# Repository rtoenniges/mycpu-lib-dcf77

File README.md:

# MyCPU_LIB_DCF77
A library written in assembler for the [MyCPU](http://www.mycpu.eu/) from Dennis Kuschel to decode the DCF77-Signal provided by an edge detection circuit.

Works also with the SCC-Rack Extension [MyCPU_PRO_SCC](https://github.com/rtoenniges/mycpu-project-slaveclock/tree/master).

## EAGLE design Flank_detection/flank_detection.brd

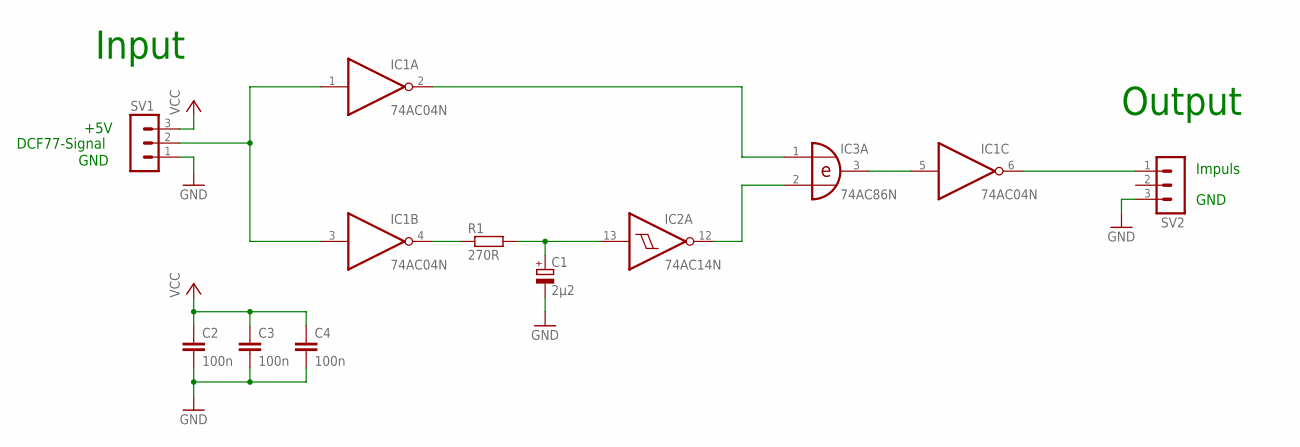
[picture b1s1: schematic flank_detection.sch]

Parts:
C1: 2µ2; E2,5-6E
C2, C3, C4: 100n; C050-024X044
IC1: 74AC04N; DIL14
IC2: 74AC14N; DIL14
IC3: 74AC86N; DIL14
R1: 270R; 0204/5
SV1, SV2: MA03-1

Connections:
GND: C1.-, C2.2, C3.2, C4.2, IC1.7 (GND), IC2.7 (GND), IC3.7 (GND), SV1.1, SV2.3
unnamed: IC1.1 (I), IC1.3 (I), SV1.2
unnamed: IC1.4 (O), R1.1
unnamed: C1.+, IC2.13 (I), R1.2
unnamed: IC1.2 (O), IC3.1 (I0)
unnamed: IC2.12 (O), IC3.2 (I1)
unnamed: IC1.5 (I), IC3.3 (O)
unnamed: IC1.6 (O), SV2.1
VCC: C2.1, C3.1, C4.1, IC1.14 (VCC), IC2.14 (VCC), IC3.14 (VCC), SV1.3

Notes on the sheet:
Input
Output
+5V
DCF77-Signal
GND
Impuls

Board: 2 copper layers, 10 parts (0 on the bottom side), 9 nets, no tracks yet.

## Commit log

2016-03-18 Added files via upload
2016-03-18 Rename sl60dcf77.asm to asm/sl60dcf77.asm
2016-03-18 Translate the comments
    Translate comments from german to english
2016-03-18 Translate comments
    Translated comments from german to english
2016-03-28 Additional comments
2016-03-28 Changed comment
2016-03-29 Listfile update
2016-03-29 Revert "Listfile update"
    This reverts commit 2b88d5d4967de4d4c234f793891d0606d7fe10c6.
2016-03-29 New feature to display synced status
    Synced status can now be displayed on the Multi-I/O-LEDs (default
    enabled).
    See "#DEFINE SYNC_DISP" line in programm
2016-03-29 Listfile updated
2016-03-31 Update and debug
    Little bit code optimizing and fixed a bug in partity checking
2016-03-31 Update and fixes
    Little bit code optimizing and fixed a bug in partity checking
2016-04-14 Move program to seperate memory page
    To save "program ram" program moved into "paged data ram"
2016-10-13 Updatet sync display and fixed error on lib calls
2017-02-20 Optimization and bug fixing
    Many many code optimizations (Memory and speed).
    Bug fixes (Mainly one big bug that couses the library to work only every
    second year)
2017-02-24 Bug fixes
2017-03-20 Added licence
2017-03-21 Edited board
2017-05-03 Add scc board
    Added #define for the scc-rack-extension
    Default is commented out
2017-05-09 Bug fix in SYNC_DISP
2017-05-10 Fixed bug in sync display
2017-05-11 Little optimizing
    In case of de synchronization more code will be skipped
2017-05-31 Termination routine changed
    Sync Ouput on SCC-Board will now set to zero on termination
2017-05-31 Little bug
    Failtest was a little hard configured :)
2024-09-01 Added meteo output
2024-09-01 Added meteo output
    Optional debugging output available
2024-09-01 Update dcf77_test.asm
    Changed to new sl60
2024-09-07 Move decoding to idle handler
2024-09-07 Litte code optimization
2024-09-07 Revert last change
2024-09-07 Code optimization (2nd try)
2024-09-27 Add handler function and data struct pointer
2024-09-30 Reduce use of ZP and secure remaining
2024-09-30 Remove tabs
2024-10-05 Add Bit 15-19
2024-10-06 Added pseudo second (59)
2024-10-06 Rename README to README.md
2024-10-13 Add FIFO as buffer
    Big stability improvement
2025-12-26 Hardened against receiver errors
2025-12-29 Change Display Init
    Added "Waiting for Sync..." and code cleanup
2025-12-29 Rebuild
2025-12-29 Bugfix Date Parity & Code Optimization
    In some cases a wrong date parity could lead to stack error.
2025-12-30 Fix Zeropage Bug
2026-01-01 Add image to README for visual reference
2026-01-01 Update GIF description in README
2026-01-01 Update animation image in README
2026-01-01 Revise image caption and add display note
    Updated image description and added a note about the display.
2026-01-01 Fix formatting and add header in README.md
2026-01-01 Fix formatting in README.md for DCF77 LCD
2026-01-04 Create C-Lib for sl60dcf77
2026-01-04 New C-Lib and Code Cleanup
    Added new C-Lib for sl60dcf77.
2026-01-04 Optimized Status LED
2026-01-04 Code Cleanup
